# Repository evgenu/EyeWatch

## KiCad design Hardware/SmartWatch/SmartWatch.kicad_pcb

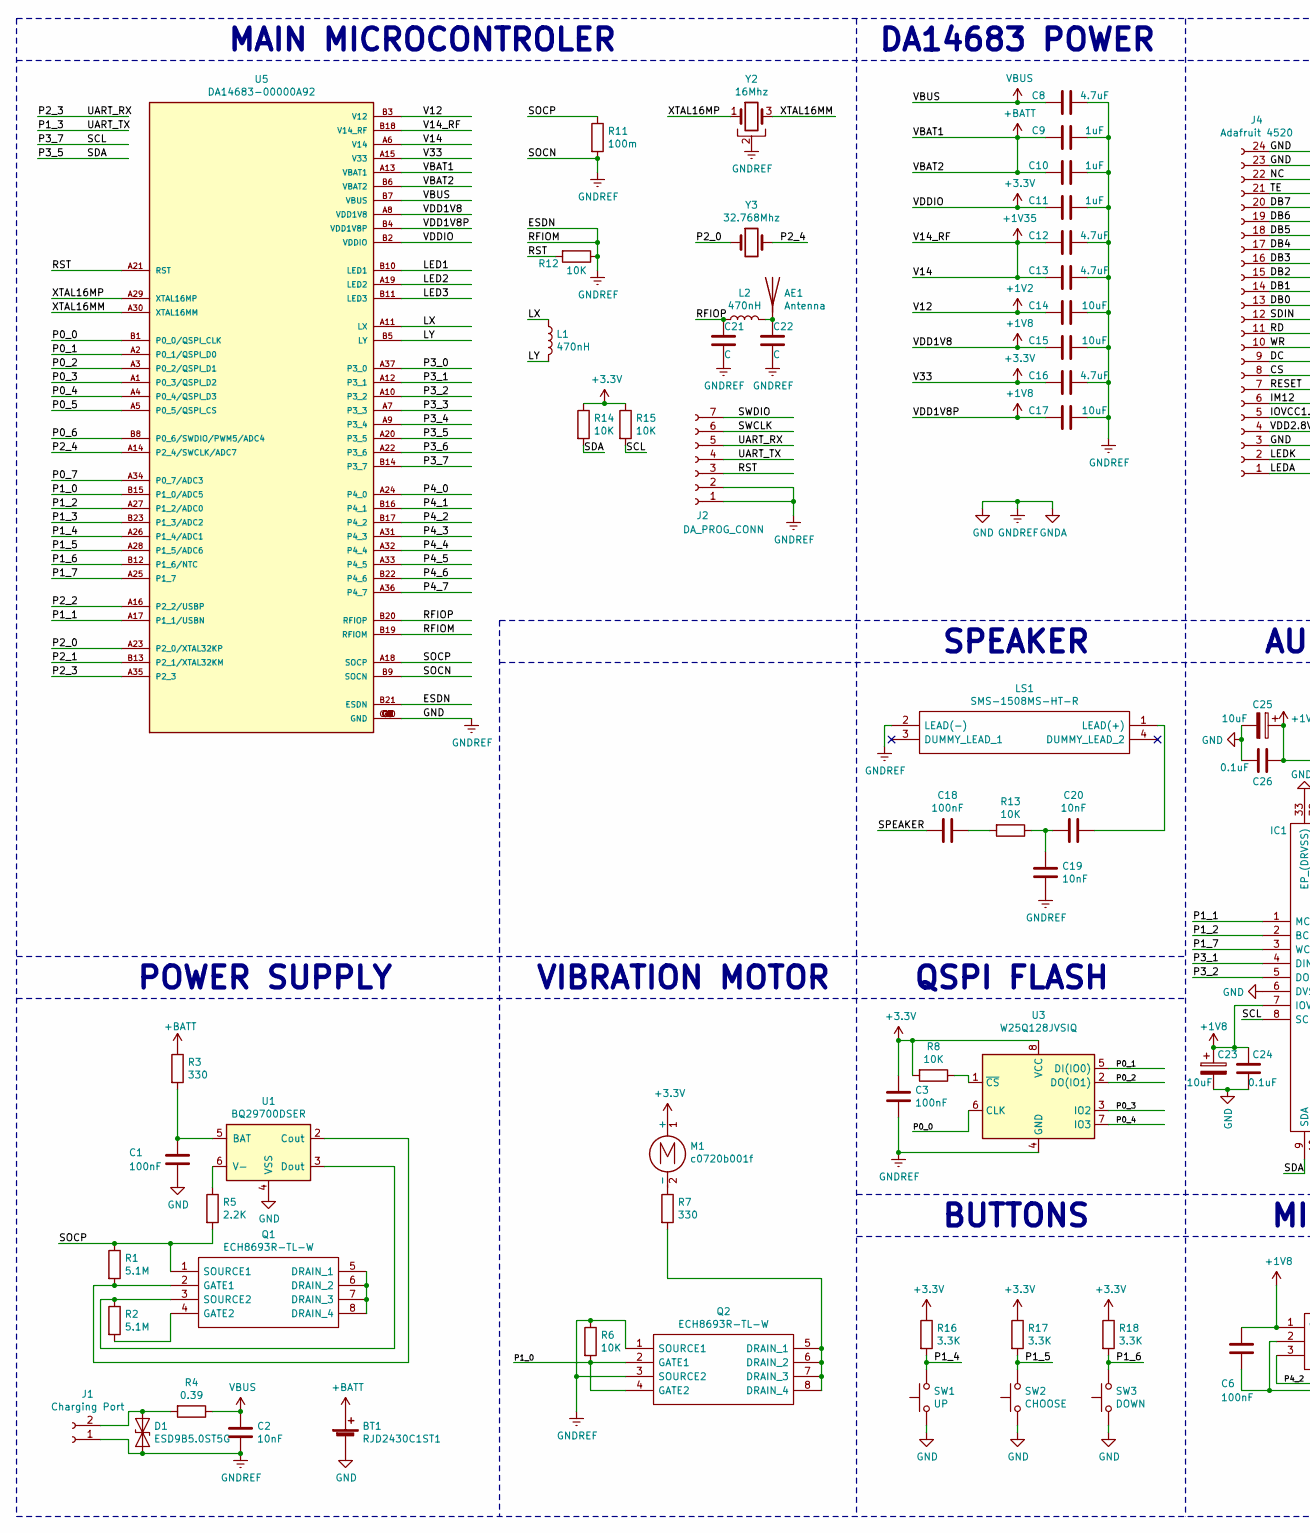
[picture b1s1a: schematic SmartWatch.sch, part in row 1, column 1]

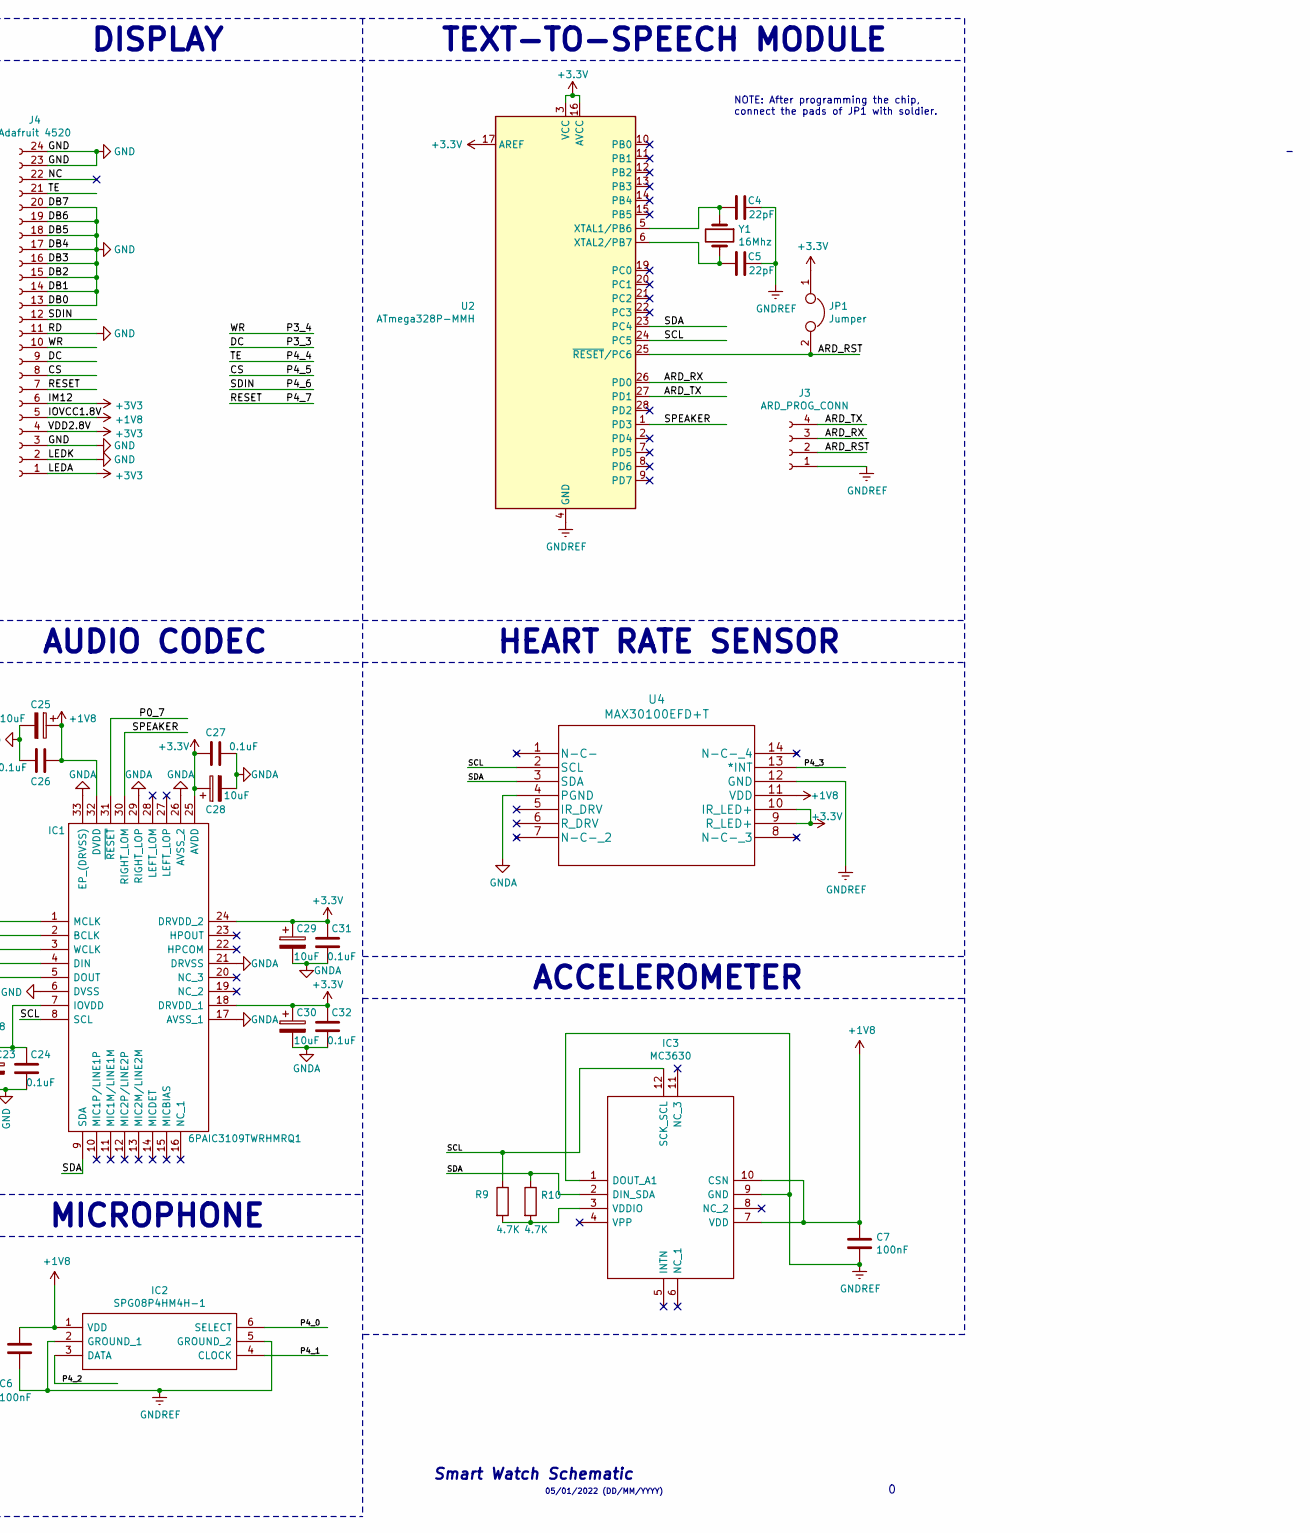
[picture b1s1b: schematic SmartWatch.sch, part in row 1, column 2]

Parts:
AE1: Antenna; Texas_SWRA117D_2.4GHz_Left
BT1: RJD2430C1ST1; PinHeader_1x02_P1.00mm_Vertical
C1, C3, C6, C7, C18: 100nF; C_01005_0402Metric
C2, C19, C20: 10nF; C_01005_0402Metric
C4, C5: 22pF; C_01005_0402Metric
C8, C12, C13, C16: 4.7uF; C_01005_0402Metric
C9, C10, C11: 1uF; C_01005_0402Metric
C14, C15, C17, C23, C25, C28, C29, C30: 10uF; C_01005_0402Metric
C21, C22: C; C_01005_0402Metric
C24, C26, C27, C31, C32: 0.1uF; C_01005_0402Metric
D1: ESD9B5.0ST5G; D_SOD-923
IC1: 6PAIC3109TWRHMRQ1; QFN50P500X500X90-33N-D; Mouser Part Number 595-6PAIC3109TWRHMRQ
IC2: SPG08P4HM4H-1; SPG08P4HM4H1; Mouser Part Number 721-SPG08P4HM4H-1
IC3: MC3630; Mouser Part Number 498-MC3630
J1: Charging Port; PinHeader_1x02_P1.00mm_Vertical
J2: DA_PROG_CONN; PinHeader_1x07_P1.00mm_Vertical_SMD_Pin1Left
J3: ARD_PROG_CONN; PinHeader_1x04_P1.00mm_Vertical_SMD_Pin1Left
J4: Adafruit 4520; Hirose_FH12-24S-0.5SH_1x24-1MP_P0.50mm_Horizontal
JP1: Jumper; SolderJumper-2_P1.3mm_Bridged2Bar_Pad1.0x1.5mm
L1, L2: 470nH; L_0402_1005Metric
LS1: SMS-1508MS-HT-R; SMS1508MSHTR; Mouser Part Number 665-SMS1508MSHTR
M1: c0720b001f; PinHeader_1x02_P1.00mm_Vertical
Q1, Q2: ECH8693R-TL-W; SOTFL65P280X95-8N; Mouser Part Number 863-ECH8693R-TL-W
R1, R2: 5.1M; R_01005_0402Metric
R3, R7: 330; R_01005_0402Metric
R4: 0.39; R_01005_0402Metric
R5: 2.2K; R_01005_0402Metric
R6, R8, R12, R13, R14, R15: 10K; R_01005_0402Metric
R9, R10: 4.7K; R_01005_0402Metric
R11: 100m; R_01005_0402Metric
R16, R17, R18: 3.3K; R_01005_0402Metric
SW1: UP; SW_Tactile_SPST_Angled_PTS645Vx58-2LFS
SW2: CHOOSE; SW_Tactile_SPST_Angled_PTS645Vx58-2LFS
SW3: DOWN; SW_Tactile_SPST_Angled_PTS645Vx58-2LFS
U1: BQ29700DSER; WSON-6_1.5x1.5mm_P0.5mm
U2: ATmega328P-MMH; QFN-28-1EP_4x4mm_P0.45mm_EP2.4x2.4mm
U3: W25Q128JVSIQ; SOIC-8_5.23x5.23mm_P1.27mm
U4: MAX30100EFD+T; MAX30100EFD&plus_
U5: DA14683-00000A92; XCVR_DA14680-01F08A92; PARTREV 5
Y1, Y2: 16Mhz; Crystal_SMD_HC49-SD
Y3: 32.768Mhz; Crystal_SMD_HC49-SD

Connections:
+1V2: C14.2, U5.B3 (V12)
+1V8: C6.1, C7.1, C15.2, C17.2, C23.1, C24.2, C25.1, C26.2, IC1.7 (IOVDD), IC1.32 (DVDD), IC2.1 (VDD), IC3.7 (VDD), IC3.10 (CSN), J4.5, U4.11 (VDD), U5.A8 (VDD1V8), U5.B4 (VDD1V8P)
+1V35: C12.2, C13.2, U5.A6 (V14), U5.B18 (V14_RF)
+BATT: BT1.1 (+), C9.2, C10.2, R3.1, U5.A13 (VBAT1), U5.B6 (VBAT2)
/ARD_RST: J3.2, JP1.2, U2.25 (~RESET~/PC6)
/ARD_RX: J3.3, U2.26 (PD0)
/ARD_TX: J3.4, U2.27 (PD1)
/CS: J4.8, U5.A33 (P4_5)
/DC: J4.9, U5.A7 (P3_3)
/LED1: U5.B10 (LED1)
/LED2: U5.A19 (LED2)
/LED3: U5.B11 (LED3)
/LX: L1.1, U5.A11 (LX)
/LY: L1.2, U5.B5 (LY)
/NC: J4.22
/P0_0: U3.6 (CLK), U5.B1 (P0_0/QSPI_CLK)
/P0_1: U3.5 (DI(IO0)), U5.A2 (P0_1/QSPI_D0)
/P0_2: U3.2 (DO(IO1)), U5.A3 (P0_2/QSPI_D1)
/P0_3: U3.3 (IO2), U5.A1 (P0_3/QSPI_D2)
/P0_4: U3.7 (IO3), U5.A4 (P0_4/QSPI_D3)
/P0_5: U5.A5 (P0_5/QSPI_CS)
/P0_6: U5.B8 (P0_6/SWDIO/PWM5/ADC4)
/P0_7: IC1.31 (~RESET), U5.A34 (P0_7/ADC3)
/P1_0: Q2.2 (GATE1), Q2.4 (GATE2), R6.2, U5.B15 (P1_0/ADC5)
/P1_1: IC1.1 (MCLK), U5.A17 (P1_1/USBN)
/P1_2: IC1.2 (BCLK), U5.A27 (P1_2/ADC0)
/P1_3: J2.4, U5.B23 (P1_3/ADC2)
/P1_4: R16.2, SW1.2, U5.A26 (P1_4/ADC1)
/P1_5: R17.2, SW2.2, U5.A28 (P1_5/ADC6)
/P1_6: R18.2, SW3.2, U5.B12 (P1_6/NTC)
/P1_7: IC1.3 (WCLK), U5.A25 (P1_7)
/P2_0: U5.A23 (P2_0/XTAL32KP), Y3.1
/P2_1: U5.B13 (P2_1/XTAL32KM)
/P2_2: U5.A16 (P2_2/USBP)
/P2_3: J2.5, U5.A35 (P2_3)
/P2_4: U5.A14 (P2_4/SWCLK/ADC7), Y3.2
/P3_0: U5.A37 (P3_0)
/P3_1: IC1.4 (DIN), U5.A12 (P3_1)
/P3_2: IC1.5 (DOUT), U5.A10 (P3_2)
/P3_4: J4.10, U5.A9 (P3_4)
/P3_5: IC1.9 (SDA), IC3.2 (DIN_SDA), R10.1, R14.2, U2.23 (PC4), U4.3 (SDA), U5.A20 (P3_5)
/P3_6: U5.A22 (P3_6)
/P3_7: IC1.8 (SCL), IC3.12 (SCK_SCL), R9.1, R15.2, U2.24 (PC5), U4.2 (SCL), U5.B14 (P3_7)
/P4_0: IC2.6 (SELECT), U5.A24 (P4_0)
/P4_1: IC2.4 (CLOCK), U5.B16 (P4_1)
/P4_2: IC2.3 (DATA), U5.B17 (P4_2)
/P4_3: U4.13 (*INT), U5.A31 (P4_3)
/P4_4: J4.21, U5.A32 (P4_4)
/P4_6: J4.12, U5.B22 (P4_6)
/P4_7: J4.7, U5.A36 (P4_7)
/RFIOP: C21.1, L2.1, U5.B20 (RFIOP)
/RST: J2.3, R12.2, U5.A21 (RST)
/SOCP: Q1.1 (SOURCE1), R1.1, R5.2, R11.1, U5.A18 (SOCP)
/SPEAKER: C18.2, IC1.30 (RIGHT_LOM), U2.1 (PD3)
/SWCLK: J2.6
/SWDIO: J2.7
/XTAL16MM: U5.A30 (XTAL16MM), Y2.3
/XTAL16MP: U5.A29 (XTAL16MP), Y2.1
GND: BT1.2 (-), C1.2, C2.2, C3.2, C4.1, C5.1, C6.2, C7.2, C8.1, C9.1, C10.1, C11.1, C12.1, C13.1, C14.1, C15.1, C16.1, C17.1, C19.2, C21.2, C22.2, C23.2, C24.1, C25.2, C26.1, C27.1, C28.2, C29.2, C30.2, C31.1, C32.1, D1.2 (A2), IC1.6 (DVSS), IC1.17 (AVSS_1), IC1.21 (DRVSS), IC1.26 (AVSS_2), IC1.29 (RIGHT_LOP), IC1.33 (EP_(DRVSS)), IC2.2 (GROUND_1), IC2.5 (GROUND_2), IC3.1 (DOUT_A1), IC3.9 (GND), J1.1, J2.1, J2.2, J3.1, J4.2, J4.3, J4.11, J4.13, J4.14, J4.15, J4.16, J4.17, J4.18, J4.19, J4.20, J4.23, J4.24, LS1.2 (LEAD(-)), Q2.1 (SOURCE1), Q2.3 (SOURCE2), R6.1, R11.2, R12.1, SW1.1, SW2.1, SW3.1, U1.4 (VSS), U2.4 (GND), U2.18 (GND), U2.29 (GND), U3.4 (GND), U4.4 (PGND), U4.12 (GND), U5.B9 (SOCN), U5.B19 (RFIOM), U5.B21 (ESDN), U5.G1 (GND), U5.G2 (GND), U5.G3 (GND), U5.G4 (GND), U5.G5 (GND), U5.G6 (GND), U5.G7 (GND), U5.G8 (GND), U5.G10 (GND), Y2.2
unnamed: AE1.1, C22.1, L2.2
unnamed: C1.1, R3.2, U1.5 (BAT)
unnamed: C4.2, U2.5 (XTAL1/PB6), Y1.1
unnamed: C5.2, U2.6 (XTAL2/PB7), Y1.2
unnamed: C18.1, R13.2
unnamed: C19.1, C20.2, R13.1
unnamed: C20.1, LS1.1 (LEAD(+))
unnamed: D1.1 (A1), J1.2, R4.2
unnamed: IC3.3 (VDDIO), R9.2, R10.2
unnamed: M1.2 (-), R7.1
unnamed: Q1.2 (GATE1), R1.2, U1.2 (Cout)
unnamed: Q1.3 (SOURCE2), R2.1, U1.3 (Dout)
unnamed: Q1.4 (GATE2), R2.2
unnamed: Q1.5 (DRAIN_1), Q1.6 (DRAIN_2), Q1.7 (DRAIN_3), Q1.8 (DRAIN_4)
unnamed: Q2.5 (DRAIN_1), Q2.6 (DRAIN_2), Q2.7 (DRAIN_3), Q2.8 (DRAIN_4), R7.2
unnamed: R5.1, U1.6 (V-)
unnamed: R8.1, U3.1 (~CS)
VBUS: C2.1, C8.2, R4.1, U5.B7 (VBUS)

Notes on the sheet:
POWER SUPPLY
VIBRATION MOTOR
QSPI FLASH
MICROPHONE
ACCELEROMETER
HEART RATE SENSOR
Smart Watch Schematic
05/01/2022 (DD/MM/YYYY)
SPEAKER
TEXT-TO-SPEECH MODULE
MAIN MICROCONTROLER
DA14683 POWER
DISPLAY
BUTTONS
AUDIO CODEC
NOTE: After programming the chip, connect the pads of JP1 with soldier.

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
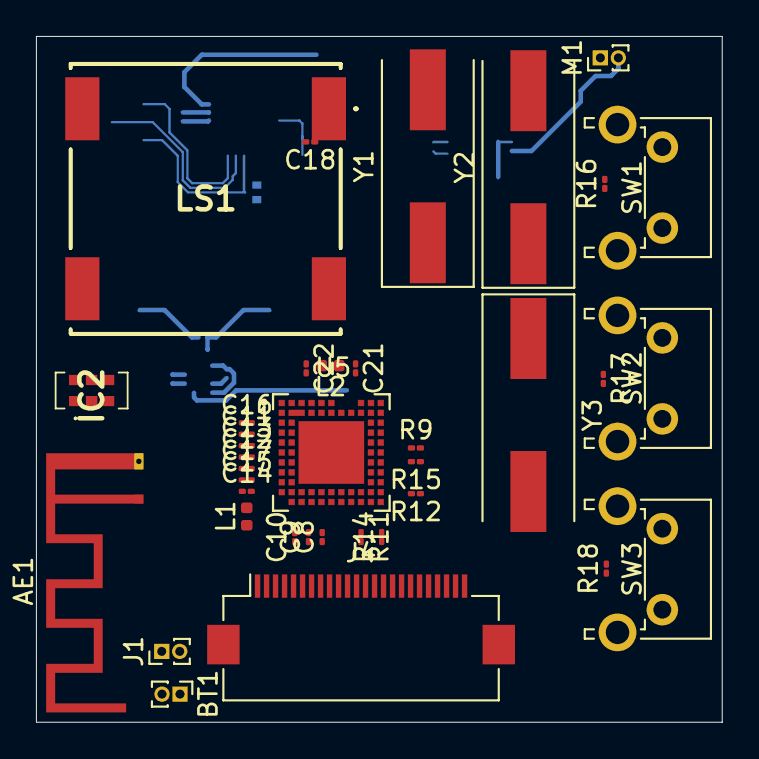
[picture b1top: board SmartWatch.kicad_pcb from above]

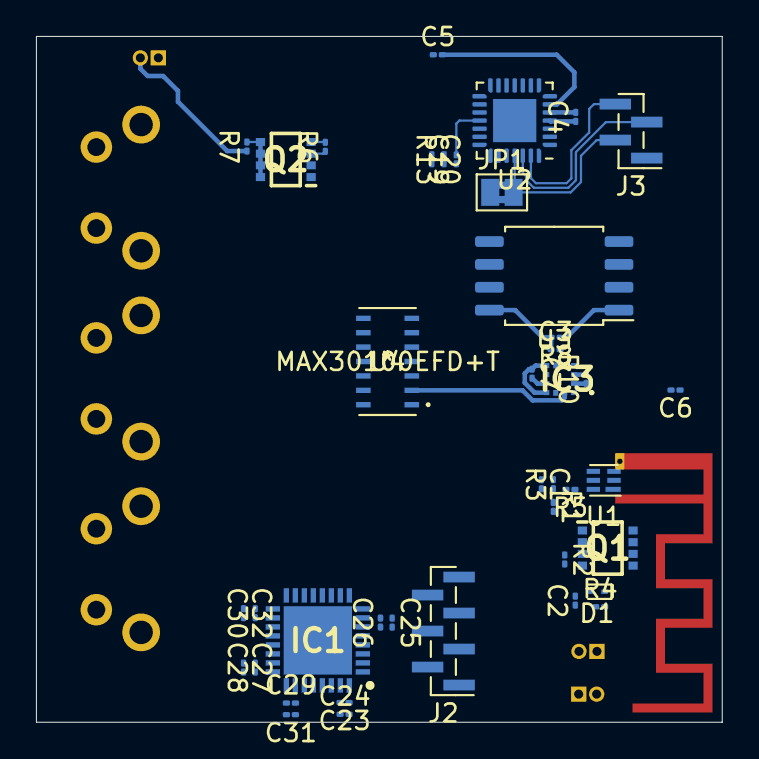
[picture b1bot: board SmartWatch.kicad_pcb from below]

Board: 6 copper layers, 38.1 x 38.1 mm, 78 parts (41 on the bottom side), 65 nets.

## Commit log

2021-12-22 [Add] Transfering work to GitHub repository.
2021-12-22 Create README.md
    Added README.md file to the GitHub repository.
2022-01-05 [Update] New footprints and new parts.
    Change in the DA14683 footprint choice - bigger package will be used. Added programming connectors for DA14683 and ARDUINO R3. I2C and UART is being added.
2022-01-05 [Update] Added CODEC and new Speaker and fixes
2022-01-13 [Update] Added Display Connector
    Added connector and fixed connector names.
2022-01-13 [Update] Full footprint assignment #1
2022-01-14 [Update] Wired Display connector to MCU.
    Communication type: SPI
2022-01-14 [Fix] Fixed ground type issues
2022-01-14 [Update] Changes to schematic and PCB test layout
2022-01-21 [Update] Added communication with codec.
2022-01-24 [Update] Schematic for review.
2022-01-25 [Update] Fixed names of certain ICs.
2022-03-09 [Update] Added BLE smartphone connection.

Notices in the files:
parts and their libraries:
Copyright 2021 Accelerated Designs. All rights reserved.
